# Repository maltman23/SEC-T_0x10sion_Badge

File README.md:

# SEC-T 0x10sion Music Synthesizer Badge kit

The SEC-T 0x10sion Music Synthesizer Badge is a kit that attendees of SEC-T 0x10sion 2024 must solder together.
It is an Arduino-compatible music synthesizer kit with:
* a touch keyboard
* built-in speaker/amp
* audio output jack (for high-quality audio)
* 5 programmable RGB LEDs

It is designed to be perfect for total beginners to learn to solder and complete successfully.

The SEC-T Synth Badge comes with a pre-programmed music synthesizer that makes way cool sounds and music and noise.
Once soldering is completed, the SEC-T Synth Badge is a really nice, portable, performing musical instrument!

The SEC-T Synth Badge kit is based on the ArduTouch music synthesizer kit by Mitch Altman / Cornfield Electronics,
which is fully Open Hardware, with a CC BY-SA 4.0 license.

The SEC-T Synth Badge makes use of a modified ArduTouch library, which is available for
programming in more super nice synthesizer features, and for making your own synthesizers.
The library comes with examples (with more to come) that serve as a nice tutorial
on how to create your own SEC-T Synth Badge synthesizers (which are Arduino sketches).

The SEC-T Synth Badge is really just an Arduino Uno clone
with the features listed above, a couple of extra buttons, and a four of pots (for playing music and controlling the sounds).
The ArduTouch Arduino Library is where the real magic comes from!

For those who want to learn more, the documentation teaches the basics of Digital Signal Processing for audio generation.

The SEC-T Synth Badge kit is fully Open Hardware, with a CC BY-SA 4.0 license.

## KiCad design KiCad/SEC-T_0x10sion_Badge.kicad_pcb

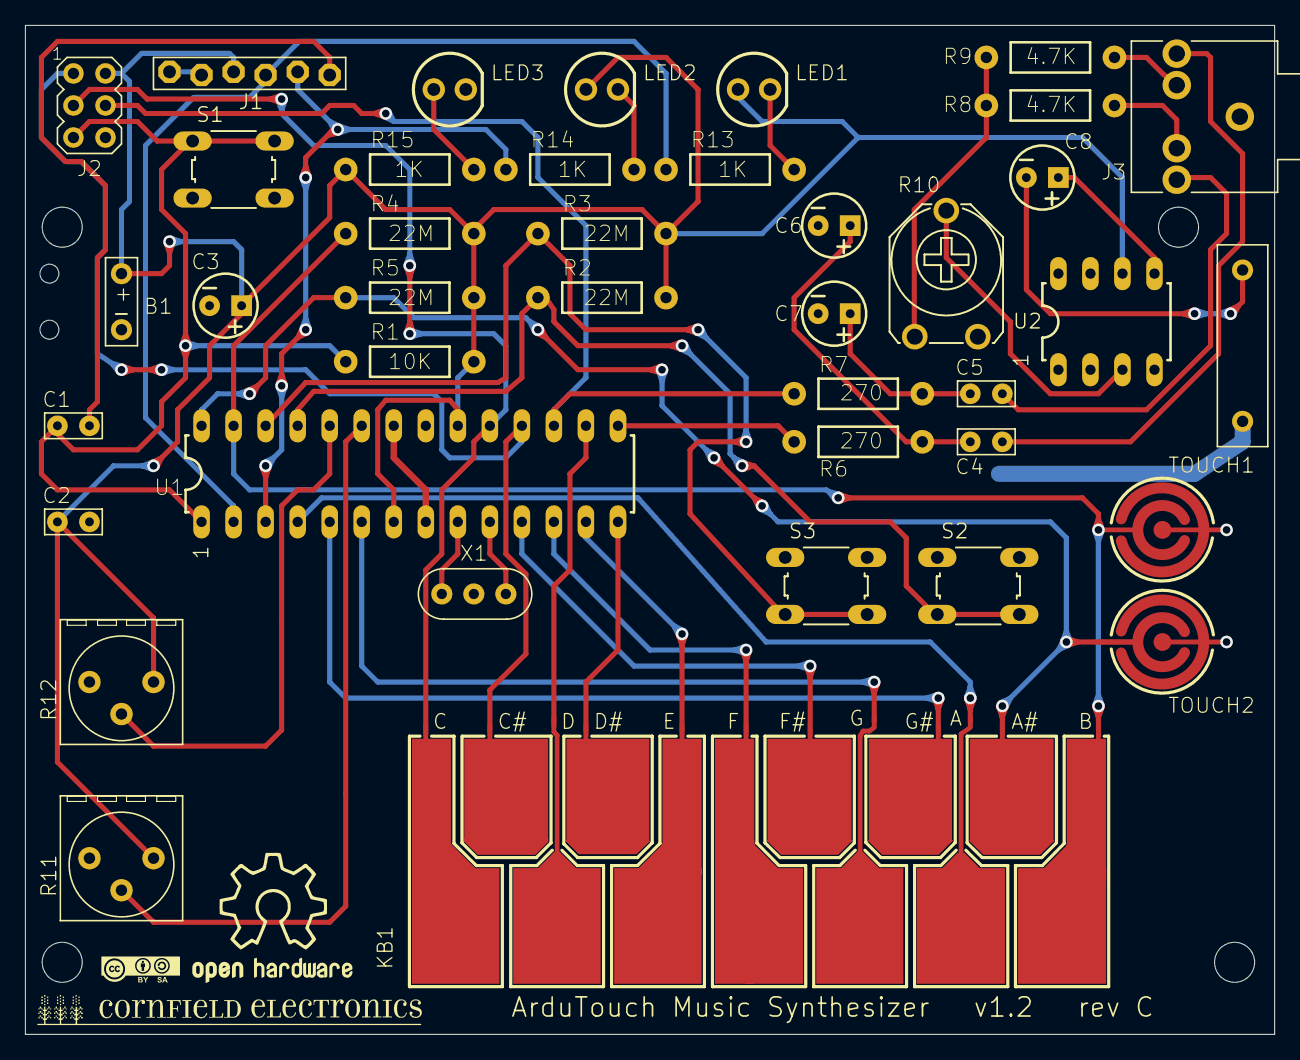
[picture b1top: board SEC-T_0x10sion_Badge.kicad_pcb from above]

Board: 2 copper layers, 99.1 x 80.0 mm, 47 parts (0 on the bottom side), 39 nets.

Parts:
@HOLE0, @HOLE1, @HOLE2, @HOLE3: (no value)
B1: BATTERY-TERMINALS
C1, C2, C4, C5: 0.1uF; CAP-PTH-SMALL
C3, C8: 100uF; CPOL-RADIAL-10UF-25V
C6, C7: 1uF; CPOL-RADIAL-10UF-25V
J1: 1X06-BIGLOCK
J2: ISP; AVRISP
J3: STEREO-AUDIO-3.5MM-SWITCHED
KB1: PCB-KEYBOARD4
LED1: Blue; LED5MM
LED2: Red; LED5MM
LED3: Green; LED5MM
R1: 10K; AXIAL-0.4
R2, R3, R4, R5: 22M; AXIAL-0.4
R6, R7: 270; AXIAL-0.4
R8, R9: 4.7K; AXIAL-0.4
R10: 10K; TRIMPOT-3319P-1
R11, R12: 10K; TRIMPOT-72PTR
R13, R14, R15: 1K; AXIAL-0.4
S1, S2, S3: TACTILE_SWITCH_6.3MM
SPKR1: SPEAKER-TERMINALS
TOUCH1, TOUCH2: PCB-TOUCHPAD2
U1: ATmega328P; DIL28-3
U2: LM386; DIP08
U$1: OSH-LOGO
U$2: CC-BY-SA-LOGO2
U$3: CORNFIELD-LOGO
X1: 16.00MHz; CERM_OSC

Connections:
A: KB1.A, U1.4
A0: R11.2, U1.23
A1: R12.2, U1.24
A2: R2.P$1, S2.3, S2.4, U1.25
A#: KB1.A#, R5.P$1, TOUCH2.1, U1.28
AUDIO-LEFT: R6.P$1, U1.15
B: KB1.B, R4.P$1, TOUCH1.1, U1.27
C+: R3.P$1, S3.3, S3.4, U1.26
D: KB1.D, U1.16
D#: KB1.D#, U1.14
E: KB1.E, U1.13
F: KB1.F, U1.12
F#: KB1.F#, U1.11
G: KB1.G, U1.6
G#: KB1.G#, U1.5
GND: B1.-, C2.2, C3.-, C6.-, C7.-, J1.1, J1.2, J2.6, J3.1, LED3.K, R10.A, R11.3, R12.3, S1.3, S1.4, S2.1, S2.2, S3.1, S3.2, SPKR1.-, TOUCH1.2, TOUCH2.2, U1.8, U1.22, U2.2, U2.4, X1.P$2
MISO: J2.1, KB1.C#, U1.18
MOSI/AUDIO-RIGHT: J2.4, R7.P$1, U1.17
unnamed: C8.-, SPKR1.+
unnamed: U1.9, X1.P$1
unnamed: U1.10, X1.P$3
unnamed: C5.1, C7.+, R7.P$2
unnamed: C8.+, U2.5
unnamed: J3.3, R8.P$2
unnamed: J3.4, R9.P$2
unnamed: R10.S, U2.3
unnamed: C5.2, J3.2
unnamed: C4.1, C6.+, R6.P$2
unnamed: LED1.K, R13.P$2
unnamed: LED2.K, R14.P$2
unnamed: C4.2, J3.5
unnamed: LED3.A, R15.P$2
unnamed: R8.P$1, R9.P$1, R10.E
RESET*: C1.1, J2.5, R1.P$1, S1.1, S1.2, U1.1
RTS*: C1.2, J1.6
RXD: J1.4, R13.P$1, U1.2
SCK: J2.3, KB1.C, U1.19
TXD: J1.5, R14.P$1, U1.3
VCC: B1.+, C2.1, C3.+, J1.3, J2.2, LED1.A, LED2.A, R1.P$2, R2.P$2, R3.P$2, R4.P$2, R5.P$2, R11.1, R12.1, R15.P$1, U1.7, U1.20, U2.6
